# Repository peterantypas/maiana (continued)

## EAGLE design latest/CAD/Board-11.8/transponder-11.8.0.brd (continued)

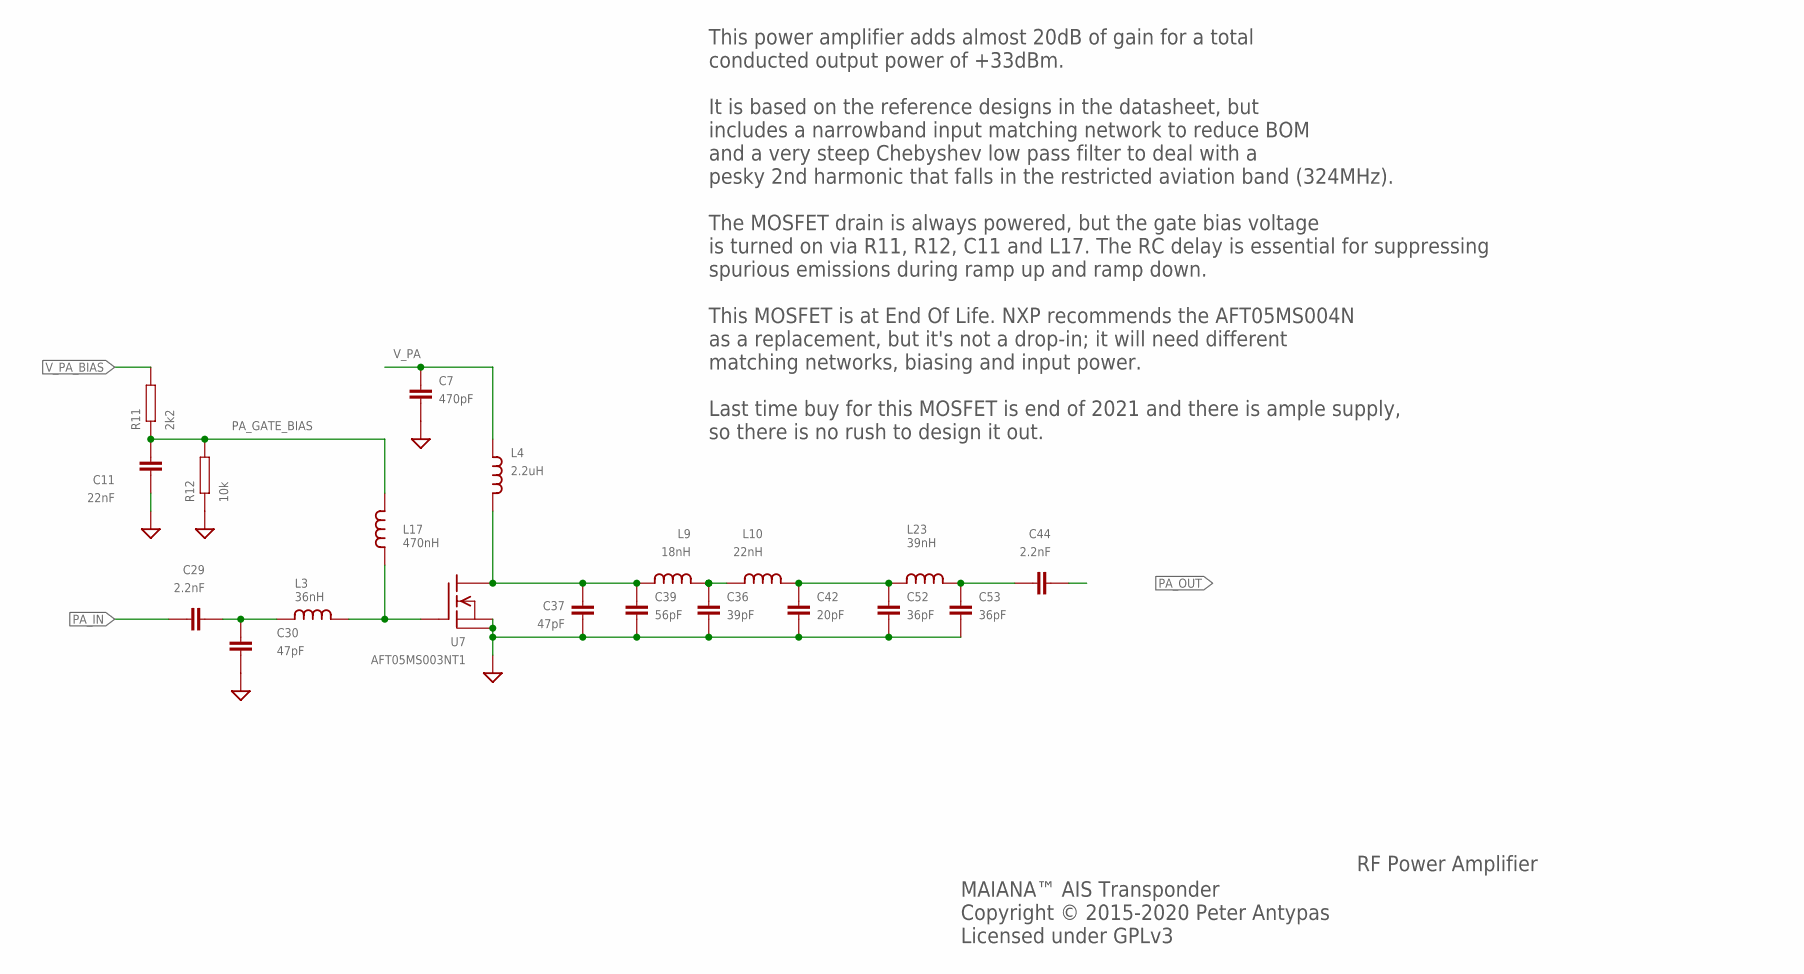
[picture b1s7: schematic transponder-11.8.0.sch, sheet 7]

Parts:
C7: 470pF; 0603; PARTNO 0603B471K500CT
C11: 22nF; 0603; PARTNO CL10B223KA8NNNC
C29, C44: 2.2nF; 0603; PARTNO 0603N222J500CT
C30, C37: 47pF; 0603; PARTNO 0603N470J500LT
C36: 39pF; 0603; PARTNO 0603N390J500CT
C39: 56pF; 0603; PARTNO 0603N560J500CT
C42: 20pF; 0603; PARTNO CL10C200JB8NNNC
C52, C53: 36pF; 0603; PARTNO 0603N360J500CT
L3: 36nH; 0603; PARTNO LQW18AN36NG00D
L4: 2.2uH; 0805; PARTNO LQM21PN2R2MGSD
L9: 18nH; 0603; PARTNO LQW18AN18NG00D
L10: 22nH; 0603; PARTNO LQW18AN22NJ00D
L17: 470nH; 0603; PARTNO HBLS1608-R47J
L23: 39nH; 0603; PARTNO LQW18AN39NG00D
R11: 2k2; 0603; PARTNO RC0603FR-072K2L
R12: 10k; 0603; PARTNO CR0603JA0103G
U7: AFT05MS003NT1; SOT-89; PARTNO AFT05MS003NT1

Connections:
GND: C7.P$2 (2), C11.P$2 (2), C30.P$2 (2), C36.P$2 (2), C37.P$2 (2), C39.P$2 (2), C42.P$2 (2), C52.P$2 (2), C53.P$2 (2), R12.P$1, U7.2 (S), U7.2@1 (PAD); also elsewhere on the board
unnamed: C37.P$1 (1), C39.P$1 (1), L4.P$2 (2), L9.P$1 (1), U7.3 (D)
unnamed: L3.P$2 (2), L17.P$1 (1), U7.1 (G)
unnamed: C36.P$1 (1), L9.P$2 (2), L10.P$1 (1)
unnamed: C29.P$2 (2), C30.P$1 (1), L3.P$1 (1)
unnamed: C42.P$1 (1), C52.P$1 (1), L10.P$2 (2), L23.P$1 (1)
unnamed: C44.P$1 (1), C53.P$1 (1), L23.P$2 (2)
PA_GATE_BIAS: C11.P$1 (1), L17.P$2 (2), R11.P$1, R12.P$2
PA_IN: C29.P$1 (1); also elsewhere on the board
PA_OUT: C44.P$2 (2); also elsewhere on the board
V_PA: C7.P$1 (1), L4.P$1 (1); also elsewhere on the board
V_PA_BIAS: R11.P$2; also elsewhere on the board

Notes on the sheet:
RF Power Amplifier
MAIANA™ AIS Transponder Copyright © 2015-2020 Peter Antypas Licensed under GPLv3
This power amplifier adds almost 20dB of gain for a total conducted output power of +33dBm. It is based on the reference designs in the datasheet, but includes a narrowband input matching network to reduce BOM and a very steep Chebyshev low pass filter to deal with a pesky 2nd harmonic that falls i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

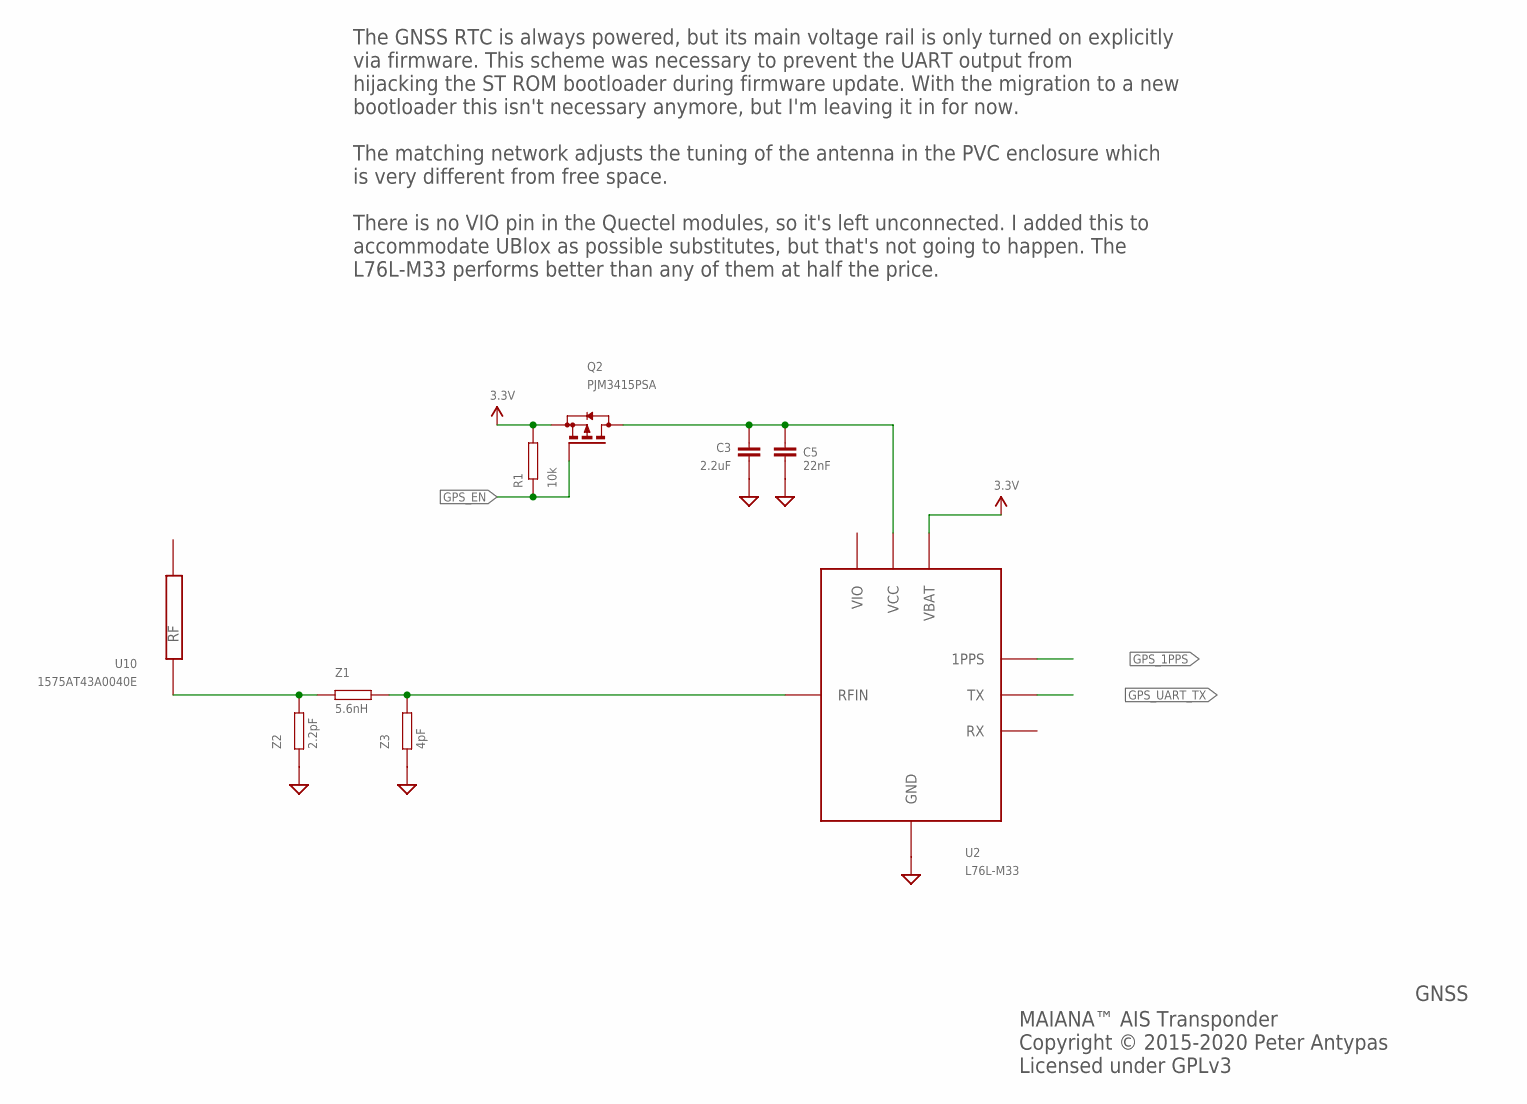
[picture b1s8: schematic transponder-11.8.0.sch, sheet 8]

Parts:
C3: 2.2uF; 0603; PARTNO 0603X225K160CT
C5: 22nF; 0603; PARTNO CL10B223KA8NNNC
Q2: PJM3415PSA; SOT23; PARTNO PJM3415PSA
R1: 10k; 0603; PARTNO CR0603JA0103G
U2: L76L-M33; GPS_MODULE; PARTNO L76L-M33
U10: 1575AT43A0040E; PARTNO 1575AT43A0040E
Z1: 5.6nH; 0603; PARTNO LQW18AN5N6C00D
Z2: 2.2pF; 0603; PARTNO 0603N2R2B500CT
Z3: 4pF; 0603; PARTNO RF18N4R0B500CT

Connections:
3.3V: Q2.2 (S), R1.P$2, U2.P$6 (VBAT); also elsewhere on the board
GND: C3.P$2 (2), C5.P$2 (2), U2.P$1 (GND), U2.P$10 (GND), U2.P$12 (GND), Z2.P$1, Z3.P$1; also elsewhere on the board
GPS_1PPS: U2.P$4 (1PPS); also elsewhere on the board
GPS_EN: Q2.1 (G), R1.P$1; also elsewhere on the board
GPS_UART_TX: U2.P$2 (TX); also elsewhere on the board
unnamed: C3.P$1 (1), C5.P$1 (1), Q2.3 (D), U2.P$8 (VCC)
unnamed: U10.P$1 (RF), Z1.P$1, Z2.P$2
unnamed: U2.P$11 (RFIN), Z1.P$2, Z3.P$2

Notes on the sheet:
GNSS
MAIANA™ AIS Transponder Copyright © 2015-2020 Peter Antypas Licensed under GPLv3
The GNSS RTC is always powered, but its main voltage rail is only turned on explicitly via firmware. This scheme was necessary to prevent the UART output from hijacking the ST ROM bootloader during firmware update. With the migration to a new bootloader this isn't necessary anymore, but I'm leaving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

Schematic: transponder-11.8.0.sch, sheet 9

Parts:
J$1: SMA_EDGE; SMA-EDGE
R4: 10k; 0603; PARTNO CR0603JA0103G
R5: 16k; 0603; PARTNO RC0603FR-0716KL
RF: TPTP10R; TP10R
SWDIO1, SWDIO2, SWDIO3, SWDIO4, SWDIO5, SWDIO6: TPTP12R; TP12R
U3: SKY13330-397LF; QFN12; PARTNO SKY13330-397LF

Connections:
3.3V: U3.P$8 (EN), U3.P$9 (VCC); also elsewhere on the board
GND: J$1.GND@0 (GND), J$1.GND@1 (GND), J$1.GND@2 (GND), J$1.GND@3 (GND), R5.P$1, SWDIO1.TP, SWDIO2.TP, SWDIO3.TP, SWDIO4.TP, SWDIO5.TP, SWDIO6.TP, U3.P$1 (GND), U3.P$3 (GND), U3.P$4 (GND), U3.P$6 (GND), U3.P$10 (GND), U3.P$12 (GND), U3.P$13 (GND); also elsewhere on the board
unnamed: J$1.SIG (SIGNAL), RF.TP, U3.P$2 (RF1)
PA_OUT: U3.P$5 (RF3); also elsewhere on the board
RF_IN: U3.P$11 (RF2); also elsewhere on the board
RX_EN: R4.P$2, R5.P$2, U3.P$7 (CTRL)
V_LNA: R4.P$1; also elsewhere on the board

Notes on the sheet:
Antenna Switch
MAIANA™ AIS Transponder Copyright © 2015-2020 Peter Antypas Licensed under GPLv3
This is a reasonably good RF switch which does not need DC blocking caps. That said, it requires control voltages to be below 2.7V, so a voltage divider was added. RX_EN must be high during RX The 9 test pads here form a footprint for a coaxial pogo pin probe in the test jig.

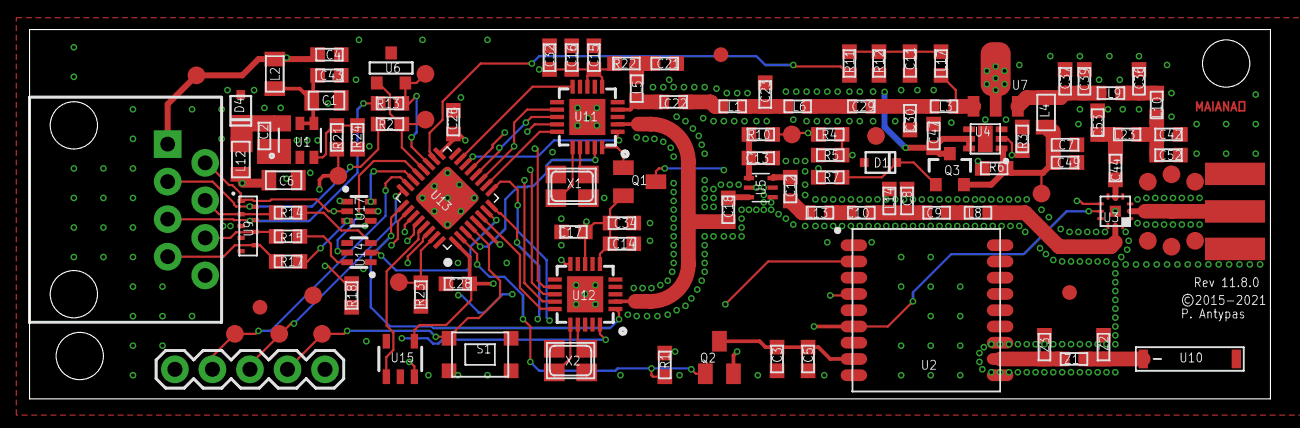
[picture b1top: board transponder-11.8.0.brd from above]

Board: 4 copper layers, 84.0 x 25.0 mm, 121 parts (0 on the bottom side), 79 nets.

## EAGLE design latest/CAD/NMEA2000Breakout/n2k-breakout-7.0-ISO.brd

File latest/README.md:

## This is the current version

This folder contains the latest and greatest. Under CAD/, you'll find directories for each board revision with associated Eagle files and exports. 

Under Firmware/ you'll find two Eclipse CDT projects. One for the transponder, and one for the NMEA 2000 adapter.

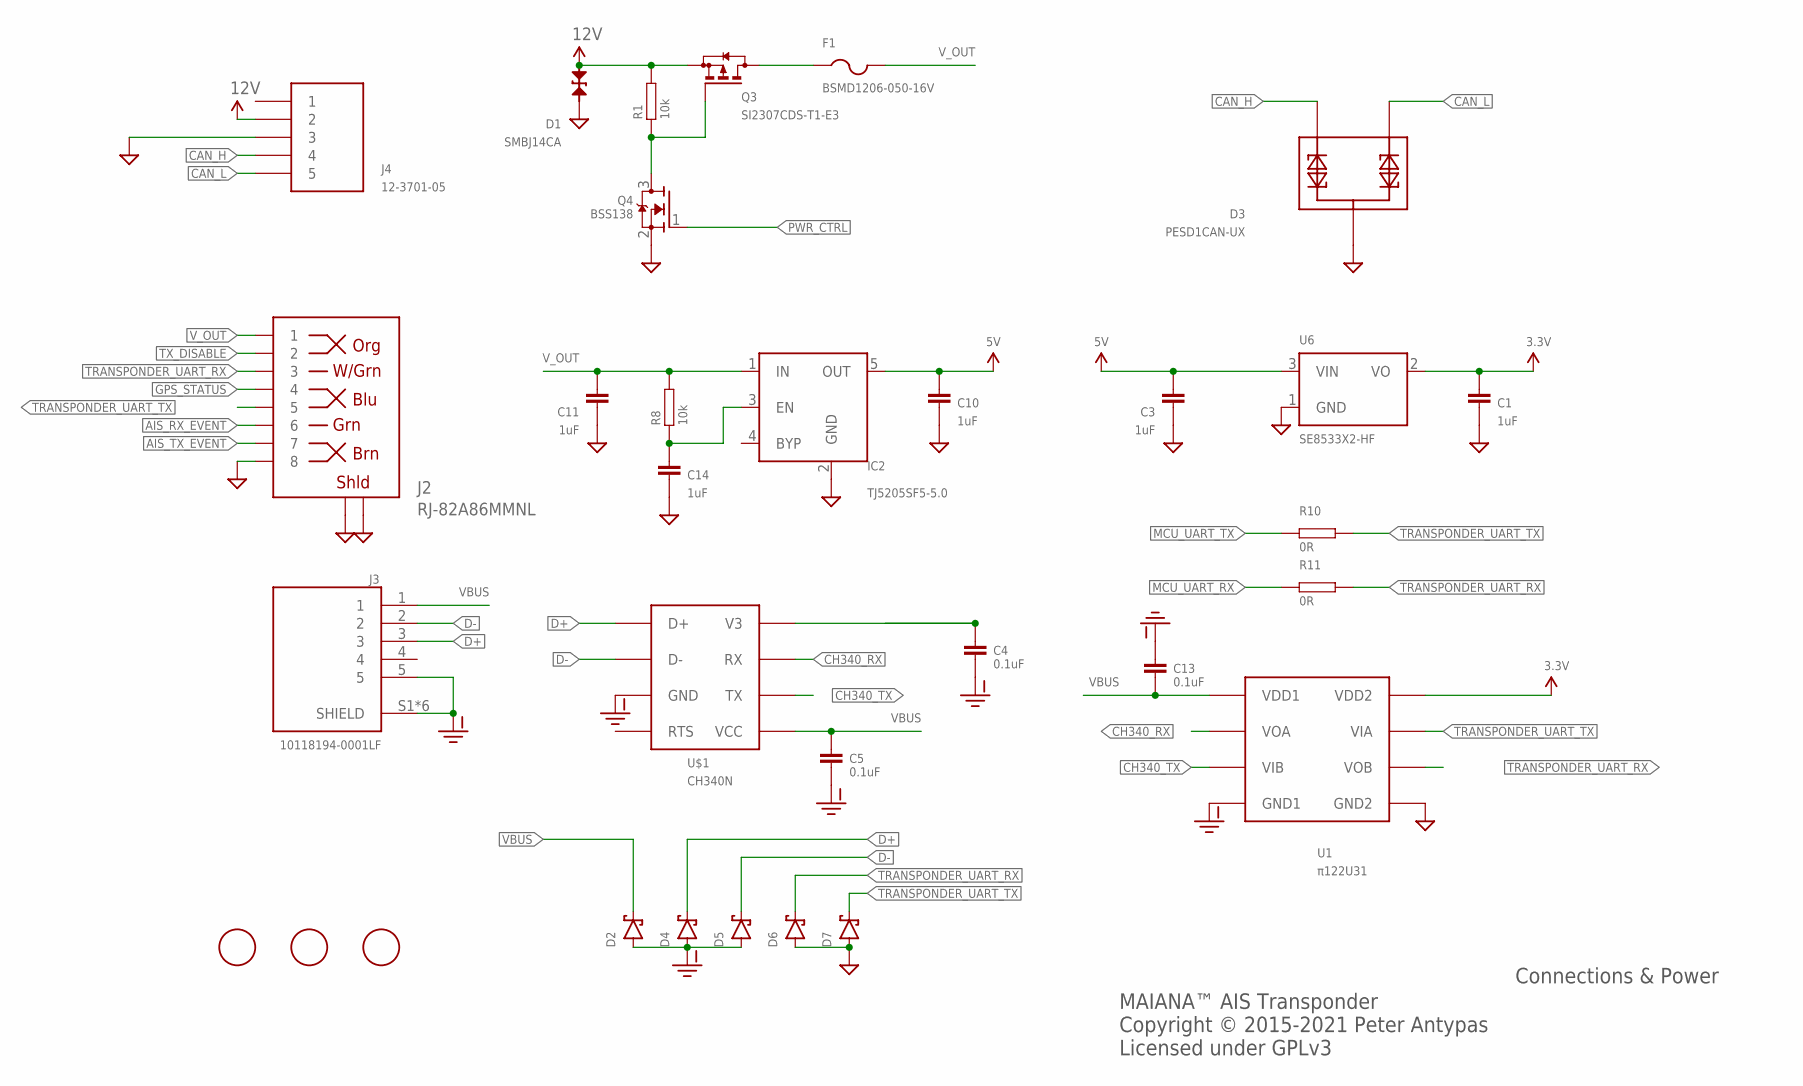
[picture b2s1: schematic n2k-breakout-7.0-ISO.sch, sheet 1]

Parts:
C1, C3, C10, C11, C14: 1uF; 0603; PARTNO CC0603KRX5R8BB105
C4, C5, C13: 0.1uF; 0603; PARTNO 06035C104KAT2A
D1: SMBJ14CA; SMB-BIDIR; PARTNO SMBJ14CA
D2, D4, D5, D6, D7: DIODE-SCHOTTKYSOD323; SOD323
D3: PESD1CAN-UX; SOT65P210X110-3N; PARTNO PESD1CAN-UX
F1: BSMD1206-050-16V; R1206; PARTNO BSMD1206-050-16V
IC2: TJ5205SF5-5.0; SOT23-5; PARTNO TJ5205SF5-5.0
J2: RJ-82A86MMNL
J3: 10118194-0001LF; AMPHENOL_10118194-0001LF; PARTNO 10118194-0001LF
J4: 12-3701-05; MICRO_C_5PIN
Q3: SI2307CDS-T1-E3; SOT23; PARTNO SI2307CDS-T1-E3
Q4: BSS138; SOT23; PARTNO BSS138
R1, R8: 10k; 0603; PARTNO RC0603FR-0710KL
R10, R11: 0R; 0603
U1: π122U31; SOIC8; PARTNO π122U31
U6: SE8533X2-HF; SOT23; PARTNO SE8533X2-HF
U$1: CH340N; SOIC-8; PARTNO CH340N
U$2, U$3, U$4: FIDUCIAL; FIDUCIAL_1MM

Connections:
3.3V: C1.P$1 (1), U1.8 (VDD2), U6.2 (VO); also elsewhere on the board
5V: C3.P$1 (1), C10.P$1 (1), IC2.5 (OUT), U6.3 (VIN); also elsewhere on the board
12V: D1.A, J4.2, Q3.2 (S), R1.P$2; also elsewhere on the board
AIS_RX_EVENT: J2.P$6 (6); also elsewhere on the board
AIS_TX_EVENT: J2.P$7 (7); also elsewhere on the board
CAN_H: D3.2, J4.4; also elsewhere on the board
CAN_L: D3.1, J4.5; also elsewhere on the board
CH340_RX: U1.2 (VOA), U$1.7 (RX)
CH340_TX: U1.3 (VIB), U$1.6 (TX)
D+: D4.C, J3.3, U$1.1 (D+)
D-: D5.C, J3.2, U$1.2 (D-)
GND: C1.P$2 (2), C3.P$2 (2), C10.P$2 (2), C11.P$2 (2), C14.P$2 (2), D1.C, D3.3, D6.A, D7.A, IC2.2 (GND), J2.P$8 (8), J2.P$9 (SHLD), J2.P$10 (SHLD), J2.P$11 (SHLD), J2.P$12 (SHLD), J4.3, Q4.2 (S), U1.5 (GND2), U6.1 (GND); also elsewhere on the board
GND-ISO: C4.P$2 (2), C5.P$2 (2), C13.P$1 (1), D2.A, D4.A, D5.A, J3.5, J3.S1 (SHIELD), J3.S2 (SHIELD), J3.S3 (SHIELD), J3.S4 (SHIELD), J3.S5 (SHIELD), J3.S6 (SHIELD), U1.4 (GND1), U$1.3 (GND)
GPS_STATUS: J2.P$4 (4); also elsewhere on the board
MCU_UART_RX: R11.P$1; also elsewhere on the board
MCU_UART_TX: R10.P$1; also elsewhere on the board
unnamed: C4.P$1 (1), U$1.8 (V3)
unnamed: Q3.1 (G), Q4.3 (D), R1.P$1
unnamed: F1.1, Q3.3 (D)
unnamed: C14.P$1 (1), IC2.3 (EN), R8.P$1
PWR_CTRL: Q4.1 (G); also elsewhere on the board
TRANSPONDER_UART_RX: D6.C, J2.P$3 (3), R11.P$2, U1.6 (VOB); also elsewhere on the board
TRANSPONDER_UART_TX: D7.C, J2.P$5 (5), R10.P$2, U1.7 (VIA); also elsewhere on the board
TX_DISABLE: J2.P$2 (2); also elsewhere on the board
VBUS: C5.P$1 (1), C13.P$2 (2), D2.C, J3.1, U1.1 (VDD1), U$1.5 (VCC)
V_OUT: C11.P$1 (1), F1.2, IC2.1 (IN), J2.P$1 (1), R8.P$2

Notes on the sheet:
MAIANA™ AIS Transponder Copyright © 2015-2021 Peter Antypas Licensed under GPLv3
Connections & Power

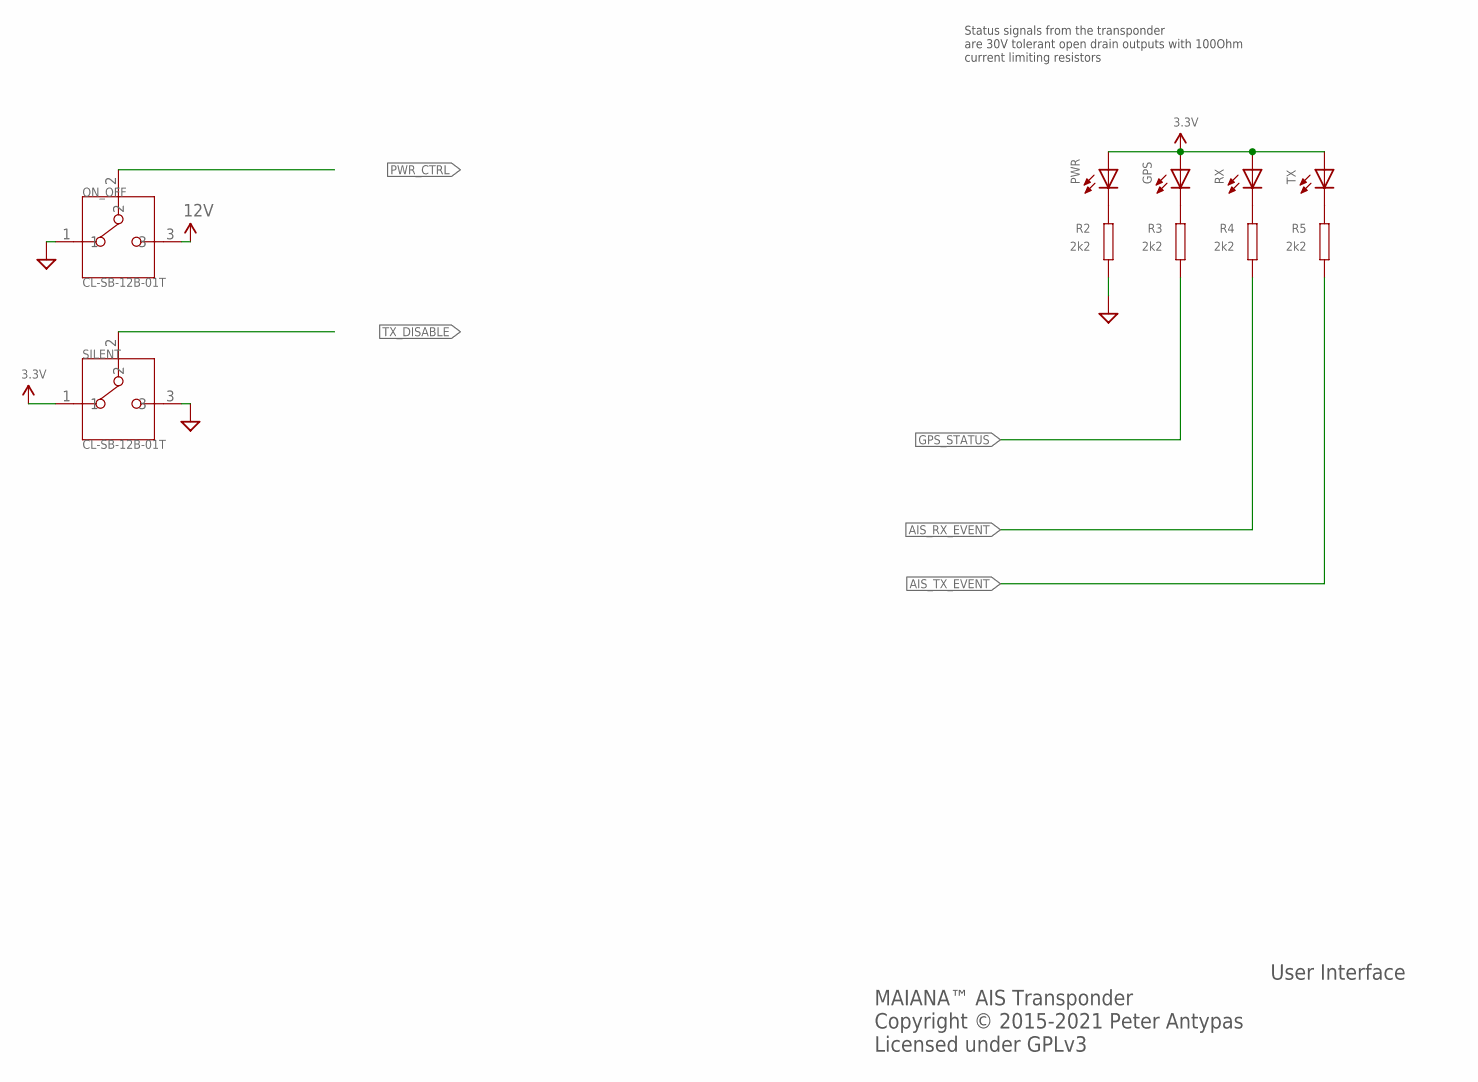
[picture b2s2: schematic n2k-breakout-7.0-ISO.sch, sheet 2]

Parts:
GPS: LEDCHIPLED_1206; CHIPLED_1206; PARTNO TJ-S3216CL9T5ALC2G-A5
ON_OFF: CL-SB-12B-01T; CL-SB-12B; PARTNO CL-SB-12B-01T
PWR: LEDCHIPLED_1206; CHIPLED_1206; PARTNO TJ-S3216CL9T5ALC2G-A5
R2, R3, R4, R5: 2k2; 0603; PARTNO CR0603-FX-2201ELF
RX: LEDCHIPLED_1206; CHIPLED_1206; PARTNO TJ-S3216CL9T5ALC2G-A5
SILENT: CL-SB-12B-01T; CL-SB-12B; PARTNO CL-SB-12B-01T
TX: LEDCHIPLED_1206; CHIPLED_1206; PARTNO TJ-S3216CL9T5ALC2G-A5

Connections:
3.3V: GPS.A, PWR.A, RX.A, SILENT.1, TX.A; also elsewhere on the board
12V: ON_OFF.3; also elsewhere on the board
AIS_RX_EVENT: R4.P$2; also elsewhere on the board
AIS_TX_EVENT: R5.P$2; also elsewhere on the board
GND: ON_OFF.1, R2.P$2, SILENT.3; also elsewhere on the board
GPS_STATUS: R3.P$2; also elsewhere on the board
unnamed: PWR.C, R2.P$1
unnamed: GPS.C, R3.P$1
unnamed: R4.P$1, RX.C
unnamed: R5.P$1, TX.C
PWR_CTRL: ON_OFF.2; also elsewhere on the board
TX_DISABLE: SILENT.2; also elsewhere on the board

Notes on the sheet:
Status signals from the transponder are 30V tolerant open drain outputs with 100Ohm current limiting resistors
MAIANA™ AIS Transponder Copyright © 2015-2021 Peter Antypas Licensed under GPLv3
User Interface

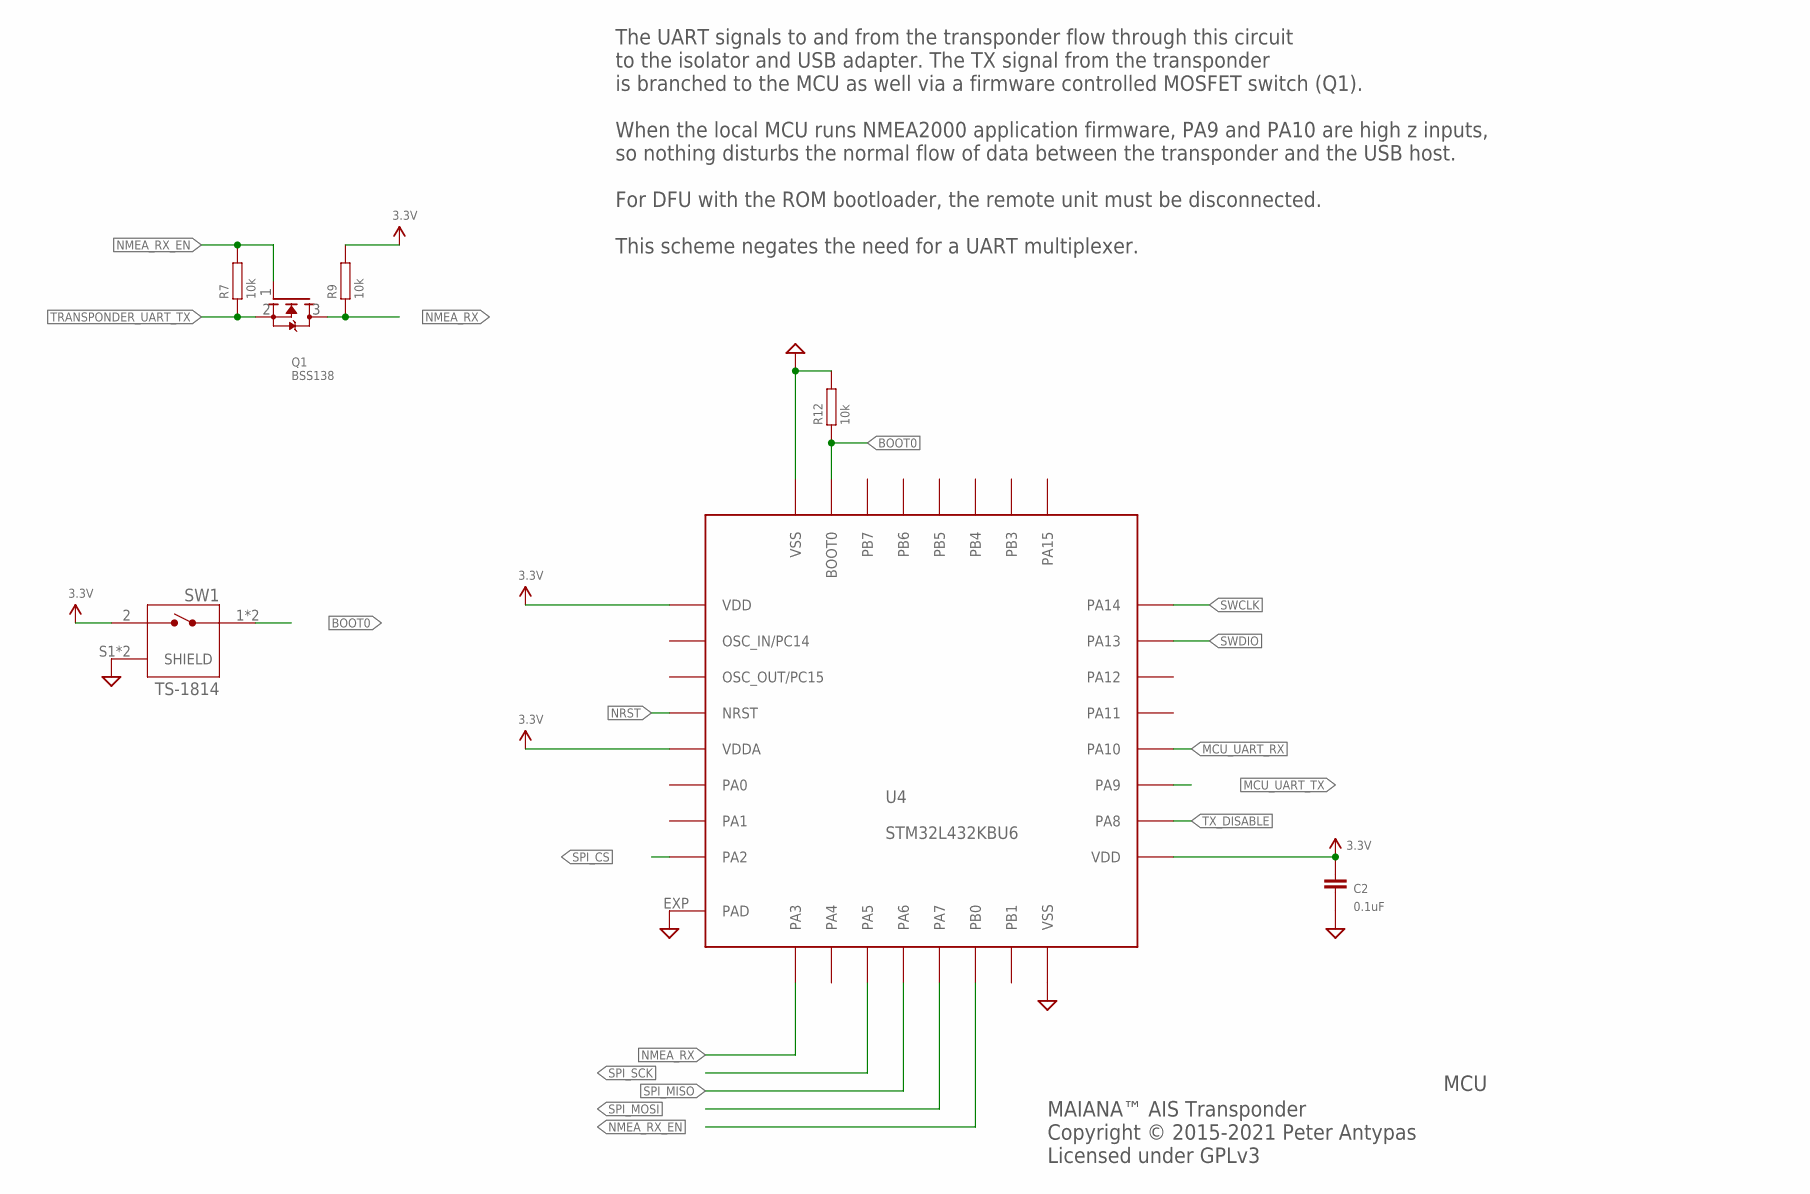
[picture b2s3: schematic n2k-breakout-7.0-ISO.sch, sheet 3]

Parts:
C2: 0.1uF; 0603; PARTNO 06035C104KAT2A
Q1: BSS138; SOT23; PARTNO BSS138
R7, R9, R12: 10k; 0603; PARTNO RC0603FR-0710KL
SW1: TS-1814; TE_1977066-1; PARTNO TS-1814
U4: STM32L432KBU6; QFN32; PARTNO STM32L422KBU6

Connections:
3.3V: C2.P$1 (1), R9.P$2, SW1.2, U4.1 (VDD), U4.5 (VDDA), U4.17 (VDD); also elsewhere on the board
BOOT0: R12.P$1, SW1.1, SW1.3 (1), U4.31 (BOOT0); also elsewhere on the board
GND: C2.P$2 (2), R12.P$2, SW1.S1 (SHIELD), SW1.S2 (SHIELD), U4.16 (VSS), U4.32 (VSS), U4.EXP (PAD); also elsewhere on the board
MCU_UART_RX: U4.20 (PA10); also elsewhere on the board
MCU_UART_TX: U4.19 (PA9); also elsewhere on the board
NMEA_RX: Q1.3 (D), R9.P$1, U4.9 (PA3)
NMEA_RX_EN: Q1.1 (G), R7.P$2, U4.14 (PB0)
NRST: U4.4 (NRST); also elsewhere on the board
SPI_CS: U4.8 (PA2); also elsewhere on the board
SPI_MISO: U4.12 (PA6); also elsewhere on the board
SPI_MOSI: U4.13 (PA7); also elsewhere on the board
SPI_SCK: U4.11 (PA5); also elsewhere on the board
SWCLK: U4.24 (PA14); also elsewhere on the board
SWDIO: U4.23 (PA13); also elsewhere on the board
TRANSPONDER_UART_TX: Q1.2 (S), R7.P$1; also elsewhere on the board
TX_DISABLE: U4.18 (PA8); also elsewhere on the board

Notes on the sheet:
MAIANA™ AIS Transponder Copyright © 2015-2021 Peter Antypas Licensed under GPLv3
MCU
The UART signals to and from the transponder flow through this circuit to the isolator and USB adapter. The TX signal from the transponder is branched to the MCU as well via a firmware controlled MOSFET switch (Q1). When the local MCU runs NMEA2000 application firmware, PA9 and PA10 are high z inpu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

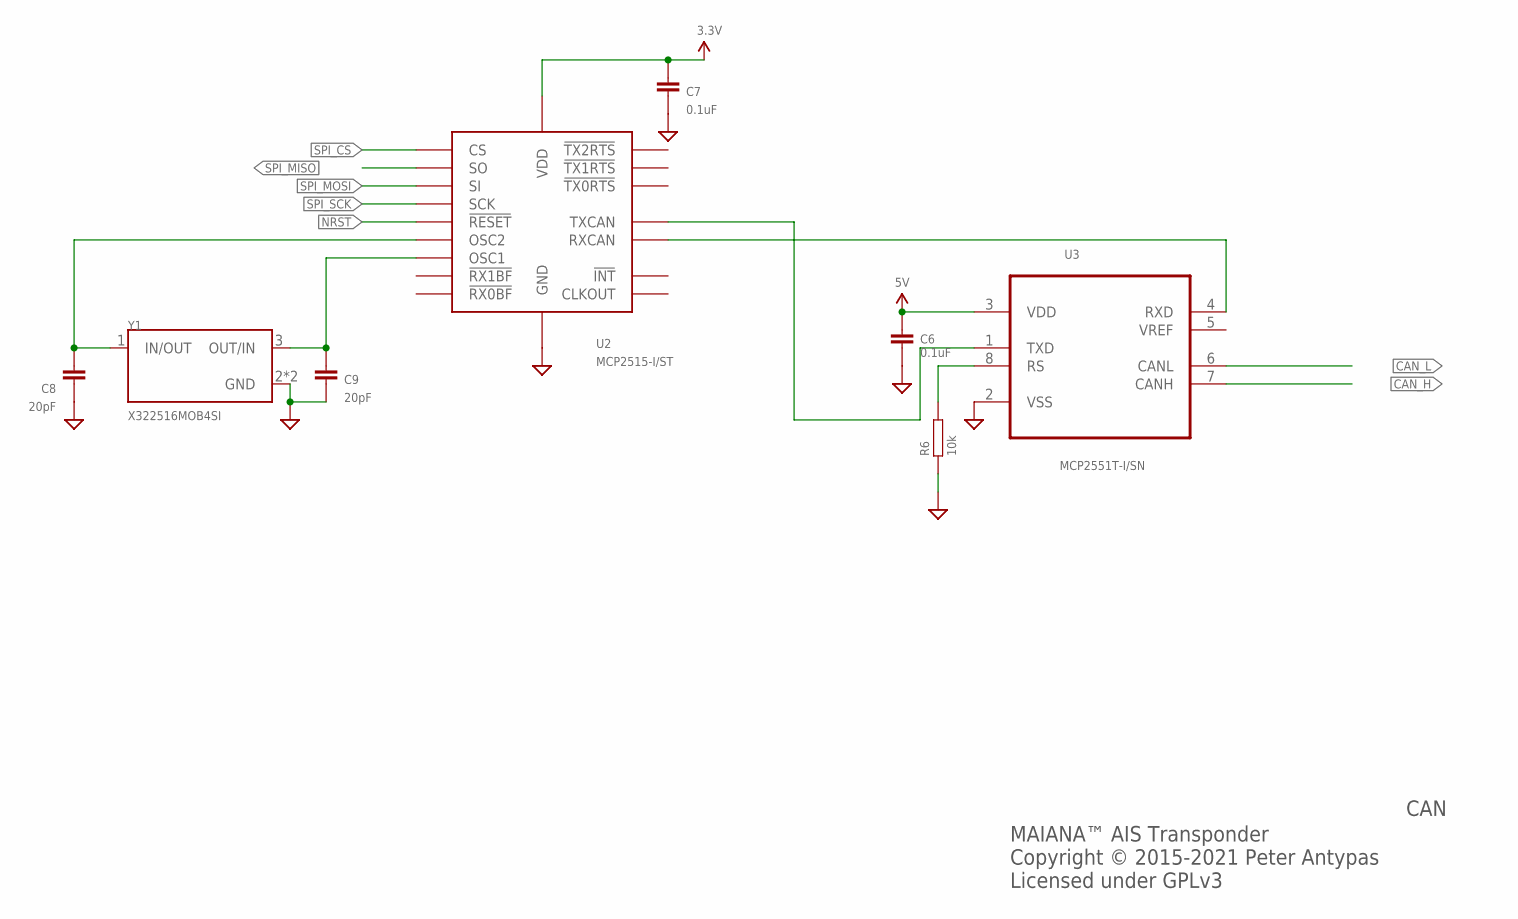
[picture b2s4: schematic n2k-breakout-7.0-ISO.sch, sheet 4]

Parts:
C6, C7: 0.1uF; 0603; PARTNO 06035C104KAT2A
C8, C9: 20pF; 0603; PARTNO GRM1885C1H200JA01D
R6: 10k; 0603; PARTNO RC0603FR-0710KL
U2: MCP2515-I/ST; TSSOP20; PARTNO MCP2515-I/ST
U3: MCP2551T-I/SN; SOIC127P600X175-8N; PARTNO MCP2551T-I/SN
Y1: X322516MOB4SI; XTAL_ECS-160-10-36-JGN-TR; PARTNO X322516MOB4SI

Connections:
3.3V: C7.P$1 (1), U2.20 (VDD); also elsewhere on the board
5V: C6.P$1 (1), U3.3 (VDD); also elsewhere on the board
CAN_H: U3.7 (CANH); also elsewhere on the board
CAN_L: U3.6 (CANL); also elsewhere on the board
GND: C6.P$2 (2), C7.P$2 (2), C8.P$2 (2), C9.P$2 (2), R6.P$1, U2.10 (GND), U3.2 (VSS), Y1.2 (GND), Y1.4 (GND); also elsewhere on the board
unnamed: R6.P$2, U3.8 (RS)
unnamed: U2.2 (RXCAN), U3.4 (RXD)
unnamed: U2.1 (TXCAN), U3.1 (TXD)
unnamed: C9.P$1 (1), U2.9 (OSC1), Y1.3 (OUT/IN)
unnamed: C8.P$1 (1), U2.8 (OSC2), Y1.1 (IN/OUT)
NRST: U2.19 (!RESET); also elsewhere on the board
SPI_CS: U2.18 (CS); also elsewhere on the board
SPI_MISO: U2.17 (SO); also elsewhere on the board
SPI_MOSI: U2.16 (SI); also elsewhere on the board
SPI_SCK: U2.14 (SCK); also elsewhere on the board

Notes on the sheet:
MAIANA™ AIS Transponder Copyright © 2015-2021 Peter Antypas Licensed under GPLv3
CAN

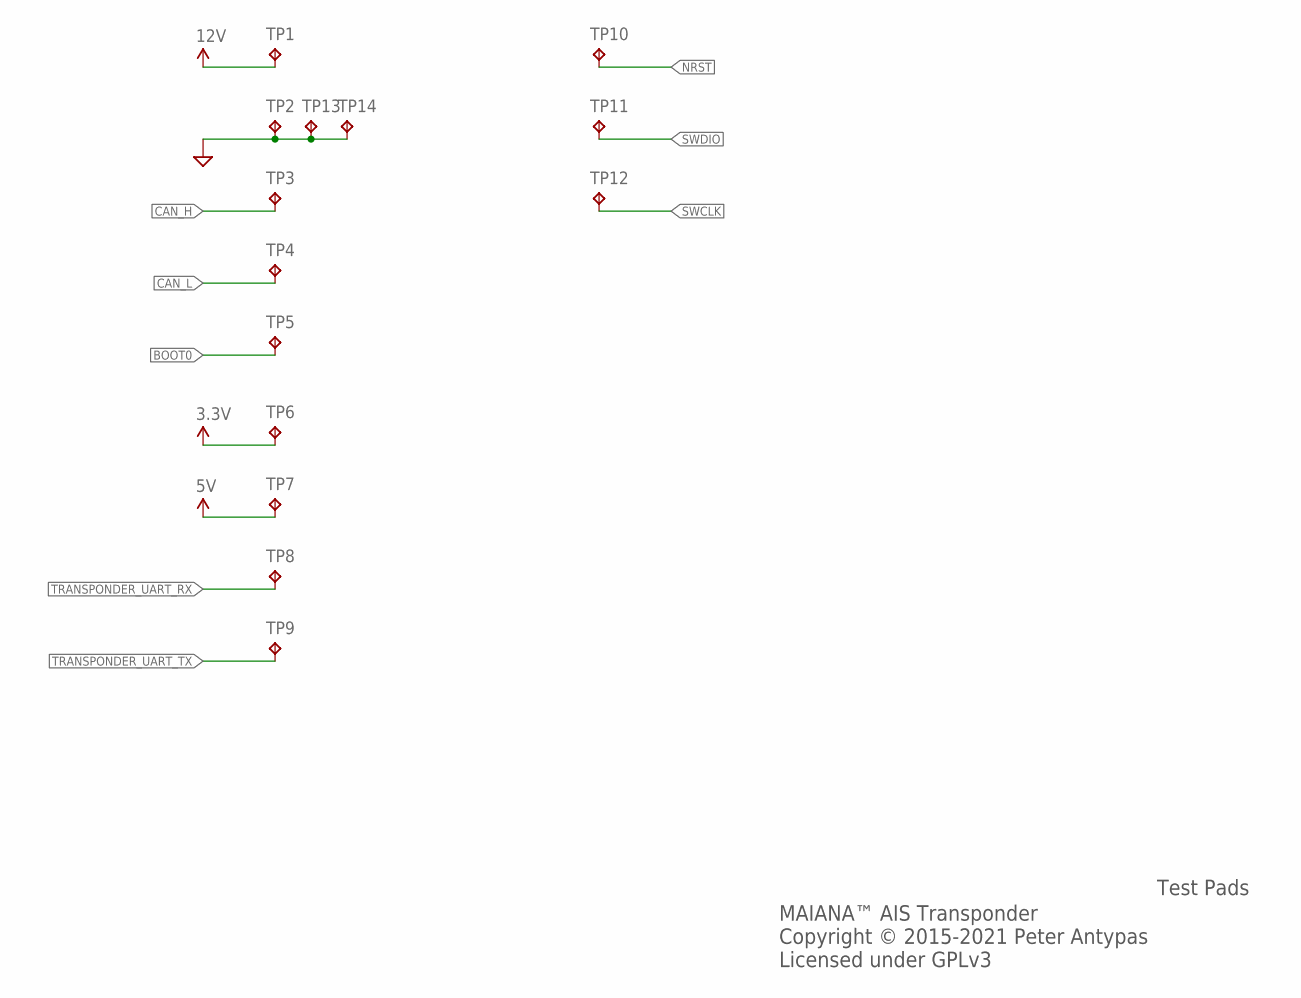
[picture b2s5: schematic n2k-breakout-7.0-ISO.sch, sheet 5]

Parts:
TP1, TP2, TP3, TP4, TP5, TP6, TP7, TP8, TP9, TP10, TP11, TP12, TP13, TP14: TPTP12R; TP12R

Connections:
3.3V: TP6.TP; also elsewhere on the board
5V: TP7.TP; also elsewhere on the board
12V: TP1.TP; also elsewhere on the board
BOOT0: TP5.TP; also elsewhere on the board
CAN_H: TP3.TP; also elsewhere on the board
CAN_L: TP4.TP; also elsewhere on the board
GND: TP2.TP, TP13.TP, TP14.TP; also elsewhere on the board
NRST: TP10.TP; also elsewhere on the board
SWCLK: TP12.TP; also elsewhere on the board
SWDIO: TP11.TP; also elsewhere on the board
TRANSPONDER_UART_RX: TP8.TP; also elsewhere on the board
TRANSPONDER_UART_TX: TP9.TP; also elsewhere on the board

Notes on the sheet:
MAIANA™ AIS Transponder Copyright © 2015-2021 Peter Antypas Licensed under GPLv3
Test Pads

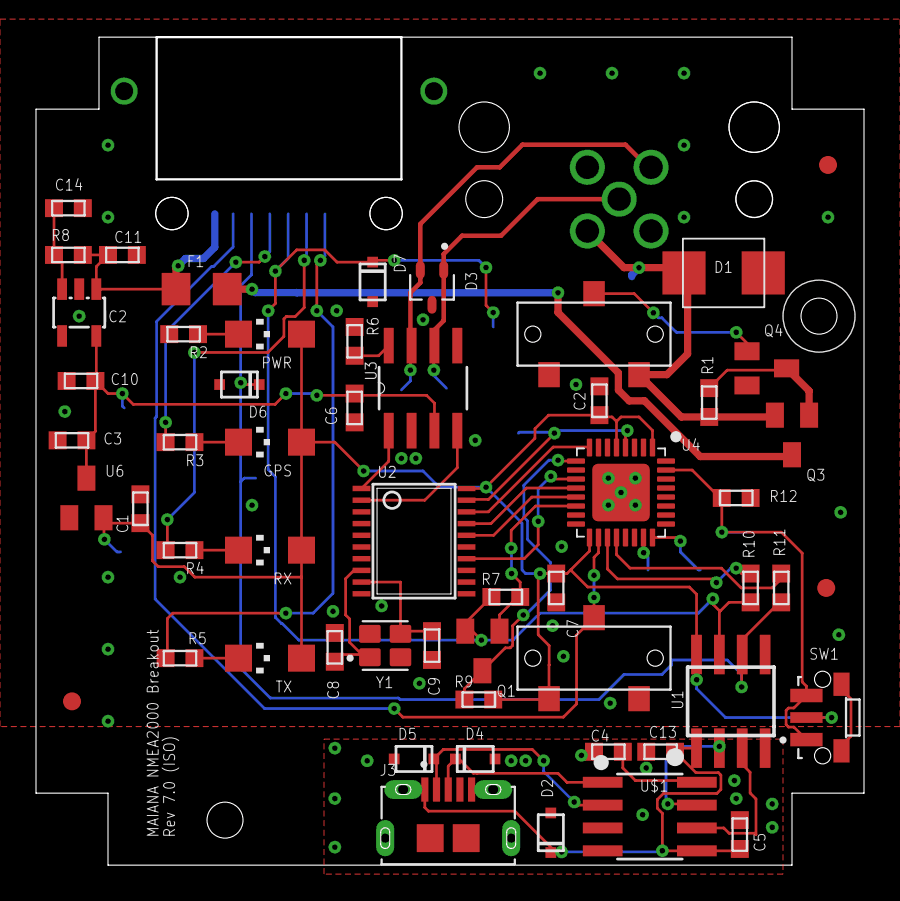
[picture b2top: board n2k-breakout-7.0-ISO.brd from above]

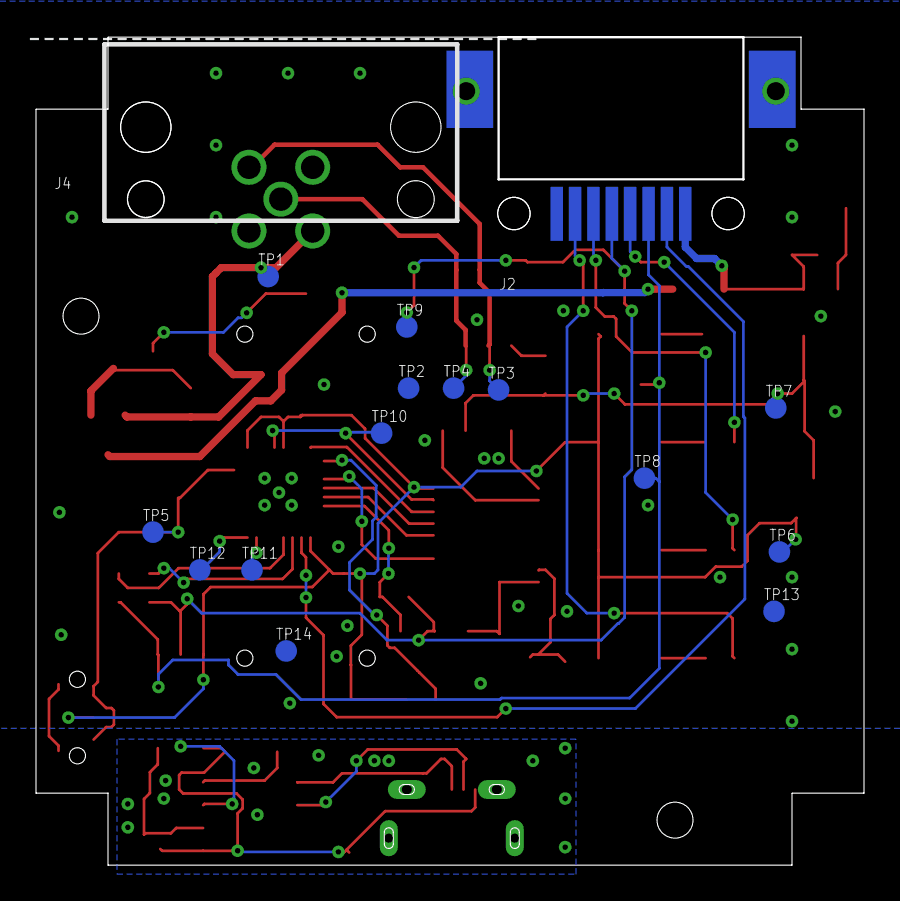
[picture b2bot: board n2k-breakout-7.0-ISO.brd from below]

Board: 2 copper layers, 45.9 x 45.9 mm, 71 parts (16 on the bottom side), 45 nets.
